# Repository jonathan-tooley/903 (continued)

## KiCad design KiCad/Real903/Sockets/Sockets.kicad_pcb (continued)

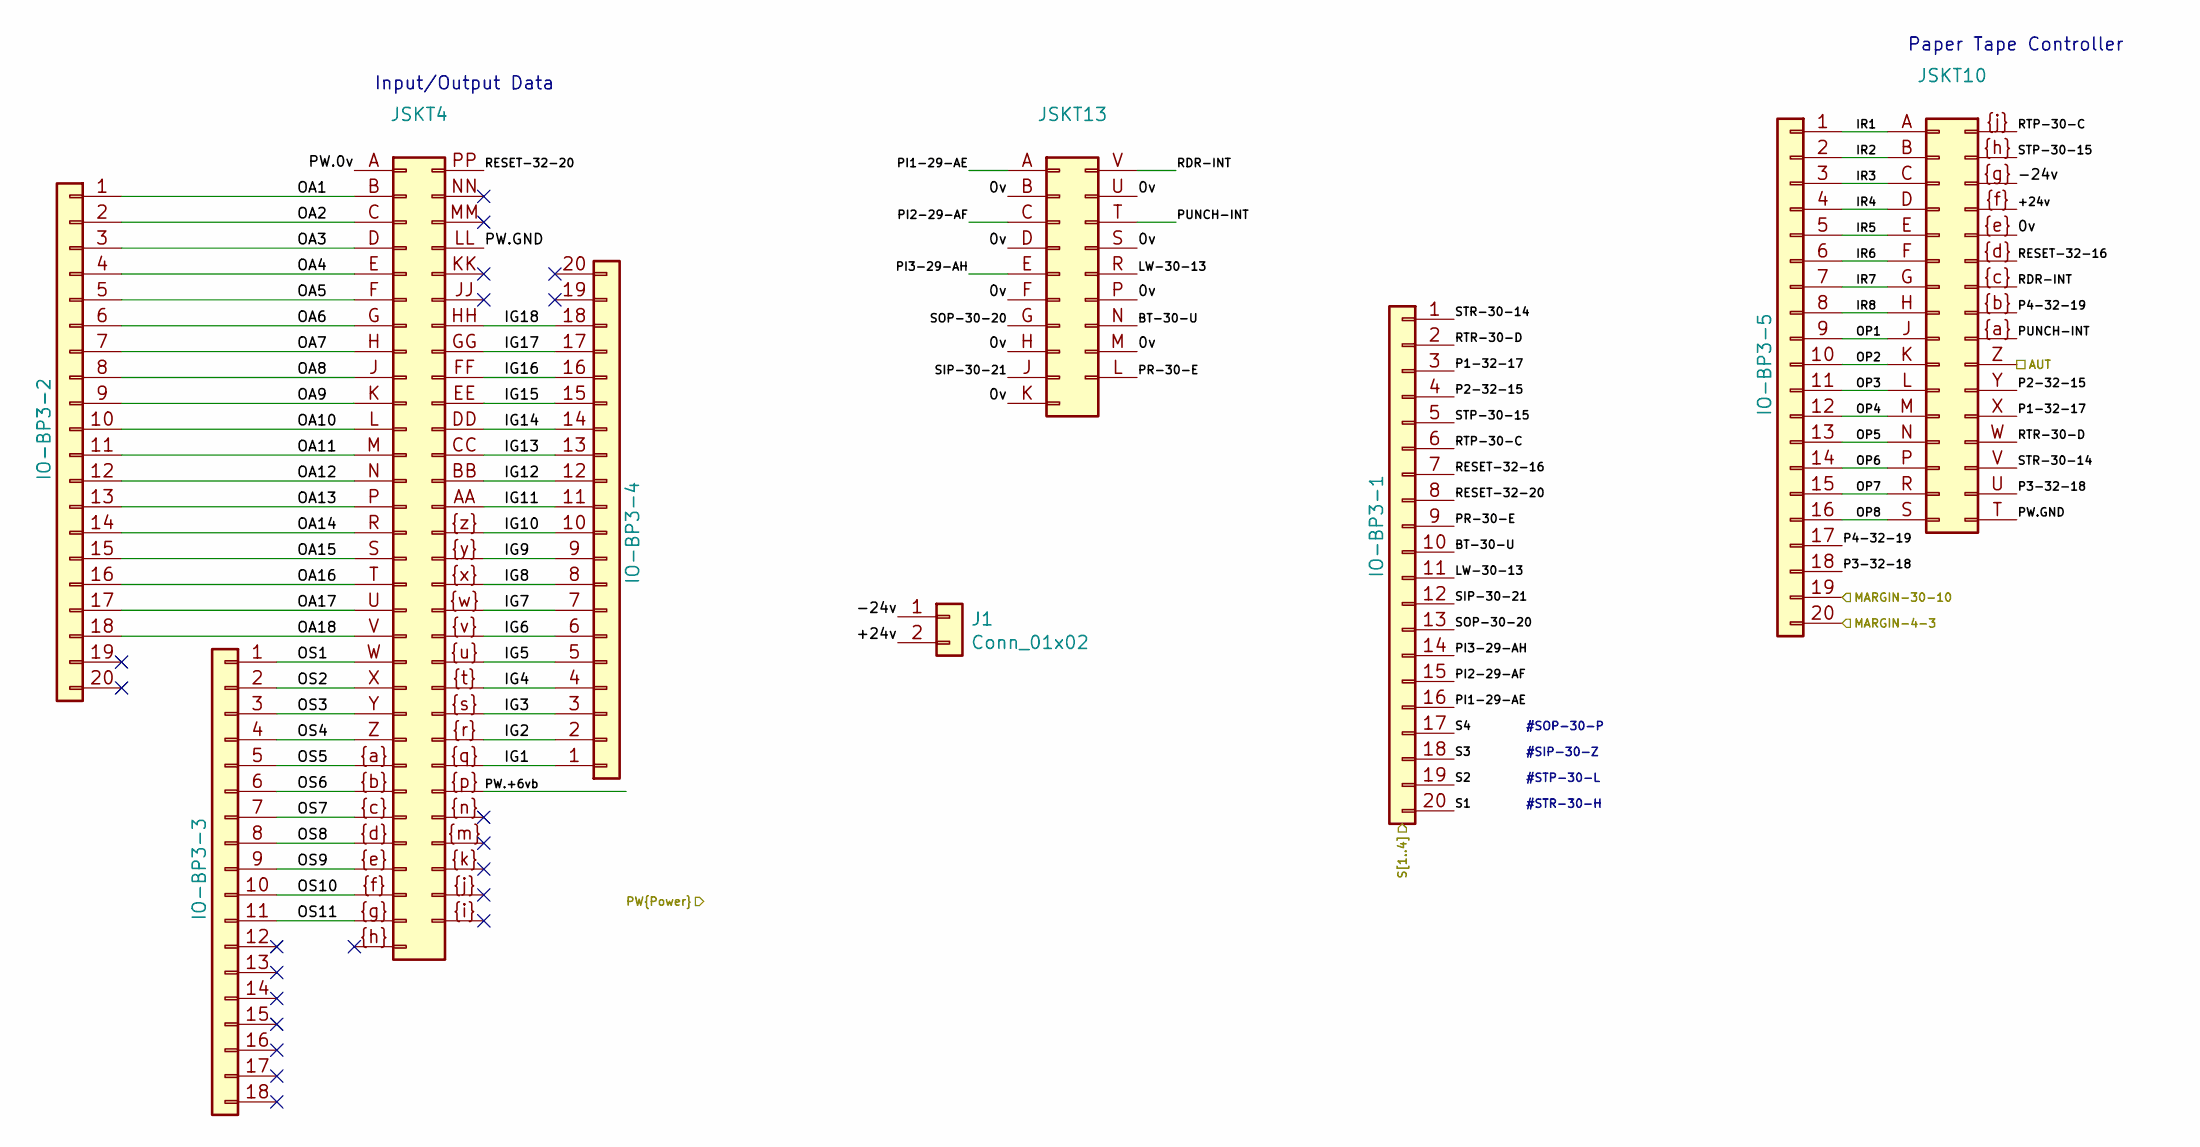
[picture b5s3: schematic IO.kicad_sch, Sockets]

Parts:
IO-BP3-1, IO-BP3-2, IO-BP3-3, IO-BP3-4, IO-BP3-5: IDC-Header_2x10_P2.54mm_Vertical
J1: Conn_01x02
JSKT4: MC61
JSKT10: MC32
JSKT13: (no value)

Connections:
/Control Unit/AUT: JSKT10.Z; also elsewhere on the board
/Control Unit/MARGIN-4-3: IO-BP3-5.20; also elsewhere on the board
/Control Unit/PW.0v: JSKT4.A; also elsewhere on the board
/Control Unit/PW.+6vb: JSKT4.~{p}; also elsewhere on the board
/Control Unit/PW.GND: JSKT4.LL, JSKT10.T; also elsewhere on the board
/Display/S1: IO-BP3-1.20; also elsewhere on the board
/Display/S2: IO-BP3-1.19; also elsewhere on the board
/Display/S3: IO-BP3-1.18; also elsewhere on the board
/Display/S4: IO-BP3-1.17; also elsewhere on the board
/IO/0v: JSKT10.~{e}, JSKT13.B, JSKT13.D, JSKT13.F, JSKT13.H, JSKT13.K, JSKT13.M, JSKT13.P, JSKT13.S, JSKT13.U
/IO/+24v: J1.2, JSKT10.~{f}
/IO/-24v: J1.1, JSKT10.~{g}
/IO/BT-30-U: IO-BP3-1.10, JSKT13.N
/IO/IG1: IO-BP3-4.1, JSKT4.~{q}
/IO/IG2: IO-BP3-4.2, JSKT4.~{r}
/IO/IG3: IO-BP3-4.3, JSKT4.~{s}
/IO/IG4: IO-BP3-4.4, JSKT4.~{t}
/IO/IG5: IO-BP3-4.5, JSKT4.~{u}
/IO/IG6: IO-BP3-4.6, JSKT4.~{v}
/IO/IG7: IO-BP3-4.7, JSKT4.~{w}
/IO/IG8: IO-BP3-4.8, JSKT4.~{x}
/IO/IG9: IO-BP3-4.9, JSKT4.~{y}
/IO/IG10: IO-BP3-4.10, JSKT4.~{z}
/IO/IG11: IO-BP3-4.11, JSKT4.AA
/IO/IG12: IO-BP3-4.12, JSKT4.BB
/IO/IG13: IO-BP3-4.13, JSKT4.CC
/IO/IG14: IO-BP3-4.14, JSKT4.DD
/IO/IG15: IO-BP3-4.15, JSKT4.EE
/IO/IG16: IO-BP3-4.16, JSKT4.FF
/IO/IG17: IO-BP3-4.17, JSKT4.GG
/IO/IG18: IO-BP3-4.18, JSKT4.HH
/IO/IR1: IO-BP3-5.1, JSKT10.A
/IO/IR2: IO-BP3-5.2, JSKT10.B
/IO/IR3: IO-BP3-5.3, JSKT10.C
/IO/IR4: IO-BP3-5.4, JSKT10.D
/IO/IR5: IO-BP3-5.5, JSKT10.E
/IO/IR6: IO-BP3-5.6, JSKT10.F
/IO/IR7: IO-BP3-5.7, JSKT10.G
/IO/IR8: IO-BP3-5.8, JSKT10.H
/IO/LW-30-13: IO-BP3-1.11, JSKT13.R
/IO/MARGIN-30-10: IO-BP3-5.19; also elsewhere on the board
/IO/OA1: IO-BP3-2.1, JSKT4.B
/IO/OA2: IO-BP3-2.2, JSKT4.C
/IO/OA3: IO-BP3-2.3, JSKT4.D
/IO/OA4: IO-BP3-2.4, JSKT4.E
/IO/OA5: IO-BP3-2.5, JSKT4.F
/IO/OA6: IO-BP3-2.6, JSKT4.G
/IO/OA7: IO-BP3-2.7, JSKT4.H
/IO/OA8: IO-BP3-2.8, JSKT4.J
/IO/OA9: IO-BP3-2.9, JSKT4.K
/IO/OA10: IO-BP3-2.10, JSKT4.L
/IO/OA11: IO-BP3-2.11, JSKT4.M
/IO/OA12: IO-BP3-2.12, JSKT4.N
/IO/OA13: IO-BP3-2.13, JSKT4.P
/IO/OA14: IO-BP3-2.14, JSKT4.R
/IO/OA15: IO-BP3-2.15, JSKT4.S
/IO/OA16: IO-BP3-2.16, JSKT4.T
/IO/OA17: IO-BP3-2.17, JSKT4.U
/IO/OA18: IO-BP3-2.18, JSKT4.V
/IO/OP1: IO-BP3-5.9, JSKT10.J
/IO/OP2: IO-BP3-5.10, JSKT10.K
/IO/OP3: IO-BP3-5.11, JSKT10.L
/IO/OP4: IO-BP3-5.12, JSKT10.M
/IO/OP5: IO-BP3-5.13, JSKT10.N
/IO/OP6: IO-BP3-5.14, JSKT10.P
/IO/OP7: IO-BP3-5.15, JSKT10.R
/IO/OP8: IO-BP3-5.16, JSKT10.S
/IO/OS1: IO-BP3-3.1, JSKT4.W
/IO/OS2: IO-BP3-3.2, JSKT4.X
/IO/OS3: IO-BP3-3.3, JSKT4.Y
/IO/OS4: IO-BP3-3.4, JSKT4.Z
/IO/OS5: IO-BP3-3.5, JSKT4.~{a}
/IO/OS6: IO-BP3-3.6, JSKT4.~{b}
/IO/OS7~{: IO-BP3-3.7, JSKT4.~{c}
/IO/OS8: IO-BP3-3.8, JSKT4.~{d}
/IO/OS9: IO-BP3-3.9, JSKT4.~{e}
/IO/OS10: IO-BP3-3.10, JSKT4.~{f}
/IO/OS11: IO-BP3-3.11, JSKT4.~{g}
/IO/P1-32-17: IO-BP3-1.3, JSKT10.X
/IO/P2-32-15: IO-BP3-1.4, JSKT10.Y
/IO/P3-32-18: IO-BP3-5.18, JSKT10.U
/IO/P4-32-19: IO-BP3-5.17, JSKT10.~{b}
/IO/PI1-29-AE: IO-BP3-1.16, JSKT13.A
/IO/PI2-29-AF: IO-BP3-1.15, JSKT13.C
/IO/PI3-29-AH: IO-BP3-1.14, JSKT13.E
/IO/PR-30-E: IO-BP3-1.9, JSKT13.L
/IO/PUNCH-INT: JSKT10.~{a}, JSKT13.T
/IO/RDR-INT: JSKT10.~{c}, JSKT13.V
/IO/RESET-32-16: IO-BP3-1.7, JSKT10.~{d}
/IO/RESET-32-20: IO-BP3-1.8, JSKT4.PP
/IO/RTP-30-C: IO-BP3-1.6, JSKT10.~{j}
/IO/RTR-30-D: IO-BP3-1.2, JSKT10.W
/IO/SIP-30-21: IO-BP3-1.12, JSKT13.J
/IO/SOP-30-20: IO-BP3-1.13, JSKT13.G
/IO/STP-30-15: IO-BP3-1.5, JSKT10.~{h}
/IO/STR-30-14: IO-BP3-1.1, JSKT10.V

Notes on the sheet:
#SIP-30-Z
#STR-30-H
#STP-30-L
Input/Output Data
#SOP-30-P
Paper Tape Controller

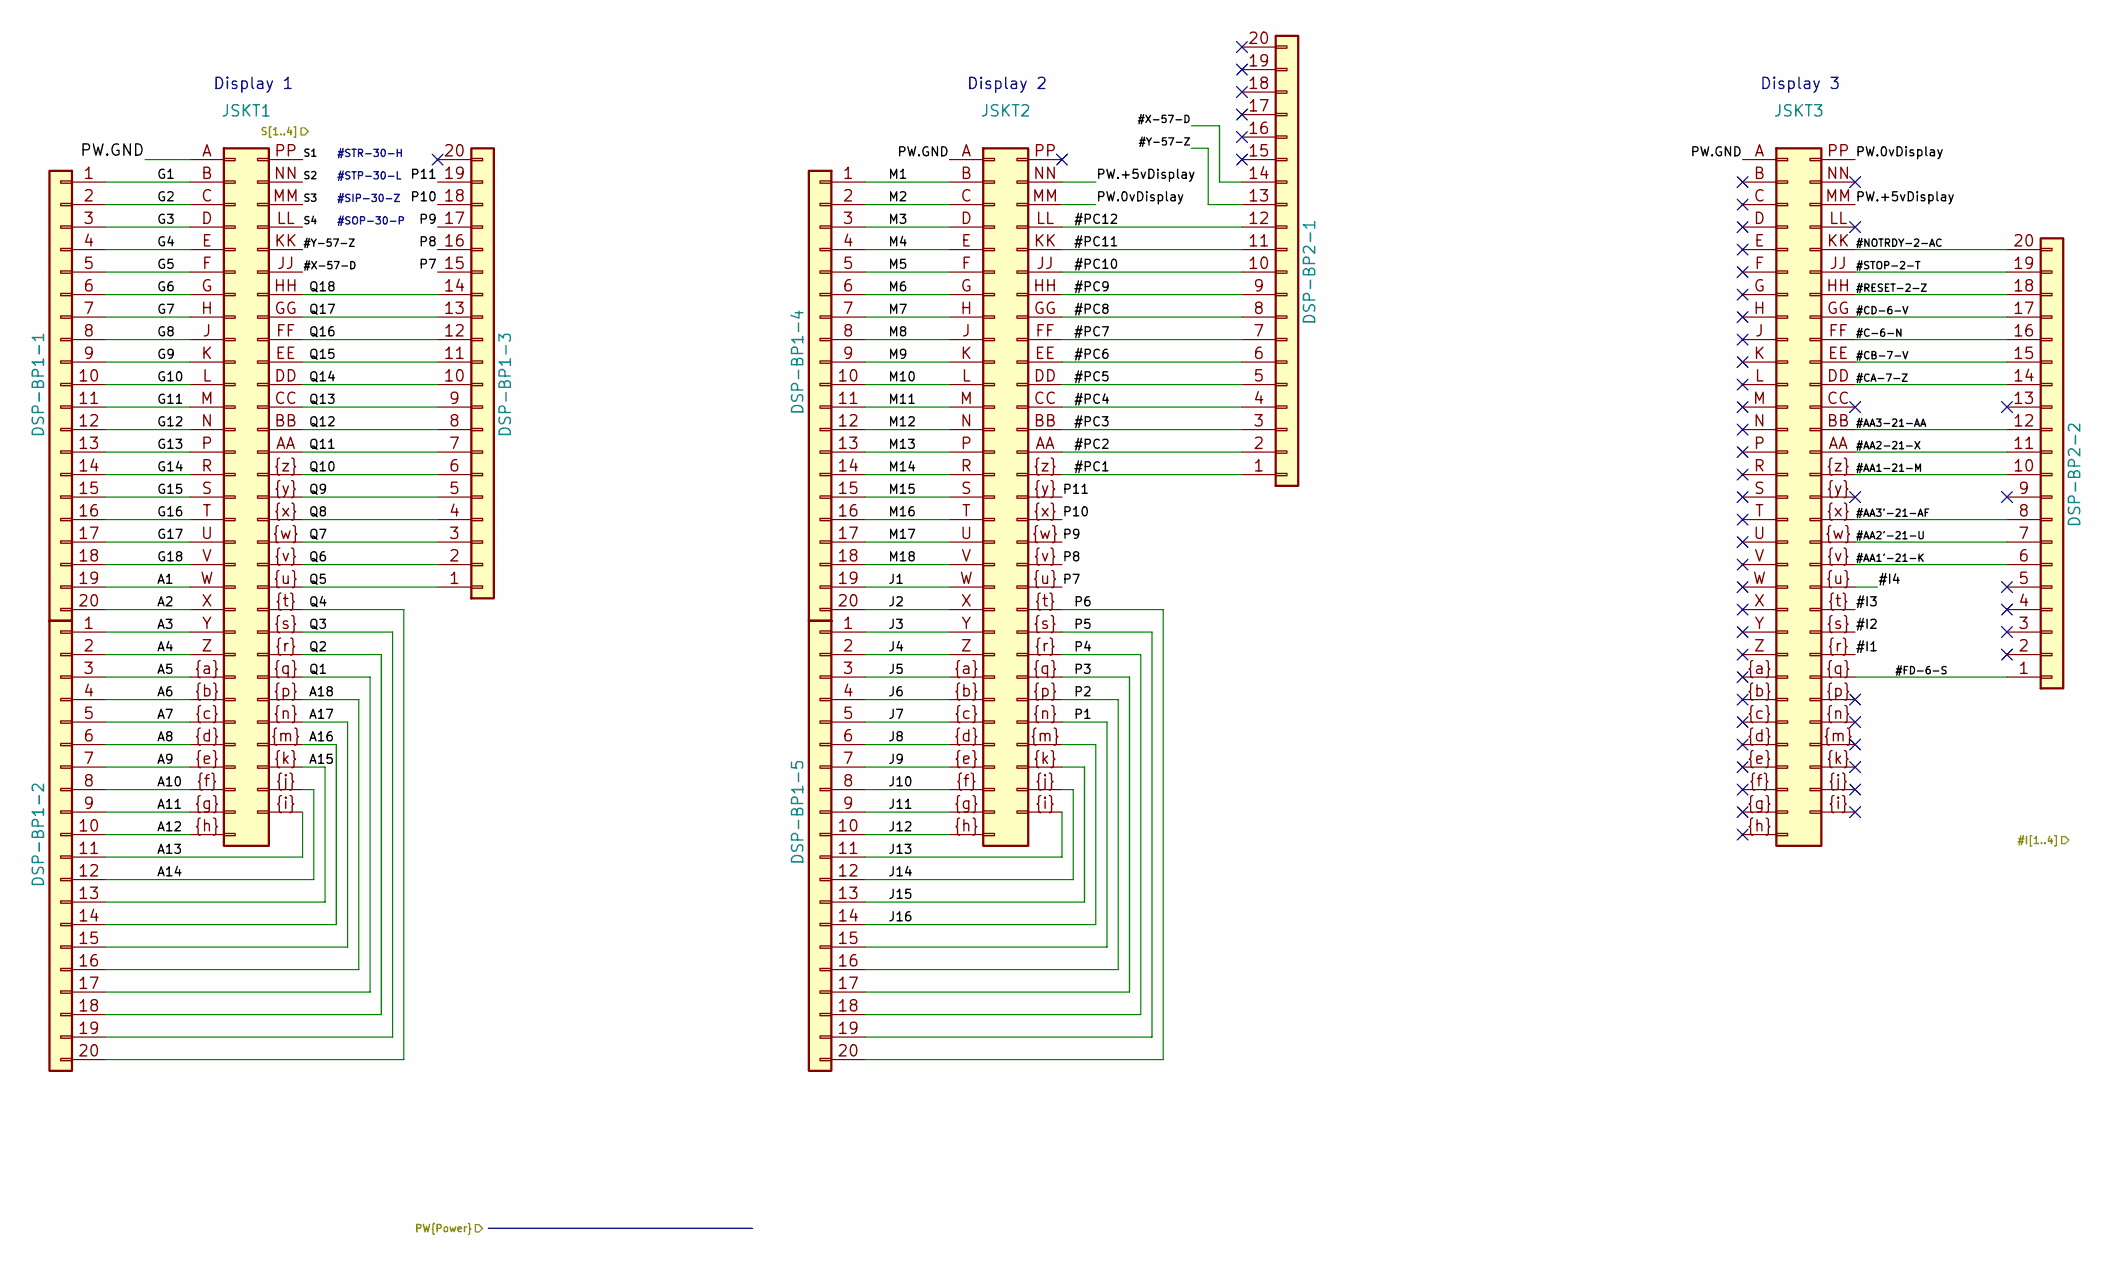
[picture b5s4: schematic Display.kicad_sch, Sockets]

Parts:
DSP-BP1-1, DSP-BP1-2, DSP-BP1-3, DSP-BP1-4, DSP-BP1-5, DSP-BP2-1, DSP-BP2-2: IDC-Header_2x10_P2.54mm_Vertical
JSKT1, JSKT2, JSKT3: MC61

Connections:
/Control Unit/#I1: JSKT3.~{r}; also elsewhere on the board
/Control Unit/#I2: JSKT3.~{s}; also elsewhere on the board
/Control Unit/#I3: JSKT3.~{t}; also elsewhere on the board
/Control Unit/#I4: JSKT3.~{u}; also elsewhere on the board
/Control Unit/PW.0vDisplay: JSKT2.MM, JSKT3.PP; also elsewhere on the board
/Control Unit/PW.+5vDisplay: JSKT2.NN, JSKT3.MM; also elsewhere on the board
/Control Unit/PW.GND: JSKT1.A, JSKT2.A, JSKT3.A; also elsewhere on the board
/Display/#AA1'-21-K: DSP-BP2-2.6, JSKT3.~{v}
/Display/#AA1-21-M: DSP-BP2-2.10, JSKT3.~{z}
/Display/#AA2'-21-U: DSP-BP2-2.7, JSKT3.~{w}
/Display/#AA2-21-X: DSP-BP2-2.11, JSKT3.AA
/Display/#AA3'-21-AF: DSP-BP2-2.8, JSKT3.~{x}
/Display/#AA3-21-AA: DSP-BP2-2.12, JSKT3.BB
/Display/#C-6-N: DSP-BP2-2.16, JSKT3.FF
/Display/#CA-7-Z: DSP-BP2-2.14, JSKT3.DD
/Display/#CB-7-V: DSP-BP2-2.15, JSKT3.EE
/Display/#CD-6-V: DSP-BP2-2.17, JSKT3.GG
/Display/#FD-6-S: DSP-BP2-2.1, JSKT3.~{q}
/Display/#NOTRDY-2-AC: DSP-BP2-2.20, JSKT3.KK
/Display/#PC1: DSP-BP2-1.1, JSKT2.~{z}
/Display/#PC2: DSP-BP2-1.2, JSKT2.AA
/Display/#PC3: DSP-BP2-1.3, JSKT2.BB
/Display/#PC4: DSP-BP2-1.4, JSKT2.CC
/Display/#PC5: DSP-BP2-1.5, JSKT2.DD
/Display/#PC6: DSP-BP2-1.6, JSKT2.EE
/Display/#PC7: DSP-BP2-1.7, JSKT2.FF
/Display/#PC8: DSP-BP2-1.8, JSKT2.GG
/Display/#PC9: DSP-BP2-1.9, JSKT2.HH
/Display/#PC10: DSP-BP2-1.10, JSKT2.JJ
/Display/#PC11: DSP-BP2-1.11, JSKT2.KK
/Display/#PC12: DSP-BP2-1.12, JSKT2.LL
/Display/#RESET-2-Z: DSP-BP2-2.18, JSKT3.HH
/Display/#STOP-2-T: DSP-BP2-2.19, JSKT3.JJ
/Display/#X-57-D: DSP-BP2-1.14, JSKT1.JJ
/Display/#Y-57-Z: DSP-BP2-1.13, JSKT1.KK
/Display/A1: DSP-BP1-1.19, JSKT1.W
/Display/A2: DSP-BP1-1.20, JSKT1.X
/Display/A3: DSP-BP1-2.1, JSKT1.Y
/Display/A4: DSP-BP1-2.2, JSKT1.Z
/Display/A5: DSP-BP1-2.3, JSKT1.~{a}
/Display/A6: DSP-BP1-2.4, JSKT1.~{b}
/Display/A7: DSP-BP1-2.5, JSKT1.~{c}
/Display/A8: DSP-BP1-2.6, JSKT1.~{d}
/Display/A9: DSP-BP1-2.7, JSKT1.~{e}
/Display/A10: DSP-BP1-2.8, JSKT1.~{f}
/Display/A11: DSP-BP1-2.9, JSKT1.~{g}
/Display/A12: DSP-BP1-2.10, JSKT1.~{h}
/Display/A13: DSP-BP1-2.11, JSKT1.~{i}
/Display/A14: DSP-BP1-2.12, JSKT1.~{j}
/Display/A15: DSP-BP1-2.13, JSKT1.~{k}
/Display/A16: DSP-BP1-2.14, JSKT1.~{m}
/Display/A17: DSP-BP1-2.15, JSKT1.~{n}
/Display/A18: DSP-BP1-2.16, JSKT1.~{p}
/Display/G1: DSP-BP1-1.1, JSKT1.B
/Display/G2: DSP-BP1-1.2, JSKT1.C
/Display/G3: DSP-BP1-1.3, JSKT1.D
/Display/G4: DSP-BP1-1.4, JSKT1.E
/Display/G5: DSP-BP1-1.5, JSKT1.F
/Display/G6: DSP-BP1-1.6, JSKT1.G
/Display/G7: DSP-BP1-1.7, JSKT1.H
/Display/G8: DSP-BP1-1.8, JSKT1.J
/Display/G9: DSP-BP1-1.9, JSKT1.K
/Display/G10: DSP-BP1-1.10, JSKT1.L
/Display/G11: DSP-BP1-1.11, JSKT1.M
/Display/G12: DSP-BP1-1.12, JSKT1.N
/Display/G13: DSP-BP1-1.13, JSKT1.P
/Display/G14: DSP-BP1-1.14, JSKT1.R
/Display/G15: DSP-BP1-1.15, JSKT1.S
/Display/G16: DSP-BP1-1.16, JSKT1.T
/Display/G17: DSP-BP1-1.17, JSKT1.U
/Display/G18: DSP-BP1-1.18, JSKT1.V
/Display/J1: DSP-BP1-4.19, JSKT2.W
/Display/J2: DSP-BP1-4.20, JSKT2.X
/Display/J3: DSP-BP1-5.1, JSKT2.Y
/Display/J4: DSP-BP1-5.2, JSKT2.Z
/Display/J5: DSP-BP1-5.3, JSKT2.~{a}
/Display/J6: DSP-BP1-5.4, JSKT2.~{b}
/Display/J7: DSP-BP1-5.5, JSKT2.~{c}
/Display/J8: DSP-BP1-5.6, JSKT2.~{d}
/Display/J9: DSP-BP1-5.7, JSKT2.~{e}
/Display/J10: DSP-BP1-5.8, JSKT2.~{f}
/Display/J11: DSP-BP1-5.9, JSKT2.~{g}
/Display/J12: DSP-BP1-5.10, JSKT2.~{h}
/Display/J13: DSP-BP1-5.11, JSKT2.~{i}
/Display/J14: DSP-BP1-5.12, JSKT2.~{j}
/Display/J15: DSP-BP1-5.13, JSKT2.~{k}
/Display/J16: DSP-BP1-5.14, JSKT2.~{m}
/Display/M1: DSP-BP1-4.1, JSKT2.B
/Display/M2: DSP-BP1-4.2, JSKT2.C
/Display/M3: DSP-BP1-4.3, JSKT2.D
/Display/M4: DSP-BP1-4.4, JSKT2.E
/Display/M5: DSP-BP1-4.5, JSKT2.F
/Display/M6: DSP-BP1-4.6, JSKT2.G
/Display/M7: DSP-BP1-4.7, JSKT2.H
/Display/M8: DSP-BP1-4.8, JSKT2.J
/Display/M9: DSP-BP1-4.9, JSKT2.K
/Display/M10: DSP-BP1-4.10, JSKT2.L
/Display/M11: DSP-BP1-4.11, JSKT2.M
/Display/M12: DSP-BP1-4.12, JSKT2.N
/Display/M13: DSP-BP1-4.13, JSKT2.P
/Display/M14: DSP-BP1-4.14, JSKT2.R
/Display/M15: DSP-BP1-4.15, JSKT2.S
/Display/M16: DSP-BP1-4.16, JSKT2.T
/Display/M17: DSP-BP1-4.17, JSKT2.U
/Display/M18: DSP-BP1-4.18, JSKT2.V
/Display/P1: DSP-BP1-5.15, JSKT2.~{n}
/Display/P2: DSP-BP1-5.16, JSKT2.~{p}
/Display/P3: DSP-BP1-5.17, JSKT2.~{q}
/Display/P4: DSP-BP1-5.18, JSKT2.~{r}
/Display/P5: DSP-BP1-5.19, JSKT2.~{s}
/Display/P6: DSP-BP1-5.20, JSKT2.~{t}
/Display/P7: DSP-BP1-3.15, JSKT2.~{u}
/Display/P8: DSP-BP1-3.16, JSKT2.~{v}
/Display/P9: DSP-BP1-3.17, JSKT2.~{w}
/Display/P10: DSP-BP1-3.18, JSKT2.~{x}
/Display/P11: DSP-BP1-3.19, JSKT2.~{y}
/Display/Q1: DSP-BP1-2.17, JSKT1.~{q}
/Display/Q2: DSP-BP1-2.18, JSKT1.~{r}
/Display/Q3: DSP-BP1-2.19, JSKT1.~{s}
/Display/Q4: DSP-BP1-2.20, JSKT1.~{t}
/Display/Q5: DSP-BP1-3.1, JSKT1.~{u}
/Display/Q6: DSP-BP1-3.2, JSKT1.~{v}
/Display/Q7: DSP-BP1-3.3, JSKT1.~{w}
/Display/Q8: DSP-BP1-3.4, JSKT1.~{x}
/Display/Q9: DSP-BP1-3.5, JSKT1.~{y}
/Display/Q10: DSP-BP1-3.6, JSKT1.~{z}
/Display/Q11: DSP-BP1-3.7, JSKT1.AA
/Display/Q12: DSP-BP1-3.8, JSKT1.BB
/Display/Q13: DSP-BP1-3.9, JSKT1.CC
/Display/Q14: DSP-BP1-3.10, JSKT1.DD
/Display/Q15: DSP-BP1-3.11, JSKT1.EE
/Display/Q16: DSP-BP1-3.12, JSKT1.FF
/Display/Q17: DSP-BP1-3.13, JSKT1.GG
/Display/Q18: DSP-BP1-3.14, JSKT1.HH
/Display/S1: JSKT1.PP; also elsewhere on the board
/Display/S2: JSKT1.NN; also elsewhere on the board
/Display/S3: JSKT1.MM; also elsewhere on the board
/Display/S4: JSKT1.LL; also elsewhere on the board

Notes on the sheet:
Display 1
#SIP-30-Z
#STR-30-H
Display 2
#STP-30-L
Display 3
#SOP-30-P

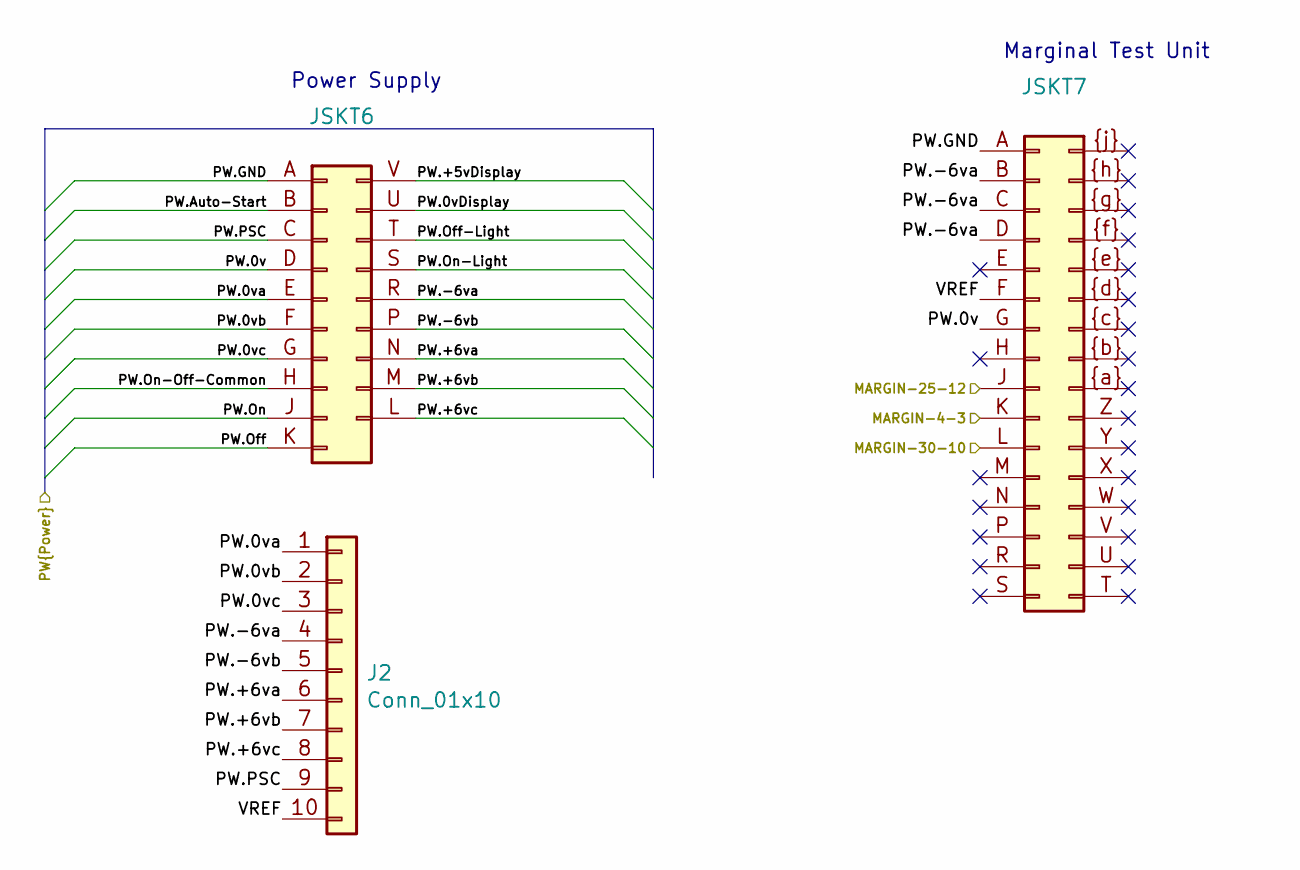
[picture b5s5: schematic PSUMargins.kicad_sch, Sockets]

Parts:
J2: Conn_01x10; Wago_734-140_1x10_P3.50mm_Vertical
JSKT6: MC19
JSKT7: MC32

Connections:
/Control Unit/MARGIN-4-3: JSKT7.K; also elsewhere on the board
/Control Unit/PW.0v: JSKT6.D, JSKT7.G; also elsewhere on the board
/Control Unit/PW.0vDisplay: JSKT6.U; also elsewhere on the board
/Control Unit/PW.0va: J2.1, JSKT6.E
/Control Unit/PW.0vb: J2.2, JSKT6.F
/Control Unit/PW.0vc: J2.3, JSKT6.G
/Control Unit/PW.+5vDisplay: JSKT6.V; also elsewhere on the board
/Control Unit/PW.+6va: J2.6, JSKT6.N; also elsewhere on the board
/Control Unit/PW.+6vb: J2.7, JSKT6.M; also elsewhere on the board
/Control Unit/PW.+6vc: J2.8, JSKT6.L
/Control Unit/PW.-6va: J2.4, JSKT6.R, JSKT7.B, JSKT7.C, JSKT7.D; also elsewhere on the board
/Control Unit/PW.-6vb: J2.5, JSKT6.P
/Control Unit/PW.Auto-Start: JSKT6.B; also elsewhere on the board
/Control Unit/PW.GND: JSKT6.A, JSKT7.A; also elsewhere on the board
/Control Unit/PW.Off: JSKT6.K; also elsewhere on the board
/Control Unit/PW.Off-Light: JSKT6.T; also elsewhere on the board
/Control Unit/PW.On: JSKT6.J; also elsewhere on the board
/Control Unit/PW.On-Light: JSKT6.S; also elsewhere on the board
/Control Unit/PW.On-Off-Common: JSKT6.H; also elsewhere on the board
/Control Unit/PW.PSC: J2.9, JSKT6.C
/IO/MARGIN-30-10: JSKT7.L; also elsewhere on the board
/PSUMargins/MARGIN-25-12: JSKT7.J
/PSUMargins/VREF: J2.10, JSKT7.F

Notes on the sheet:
Power Supply
Marginal Test Unit

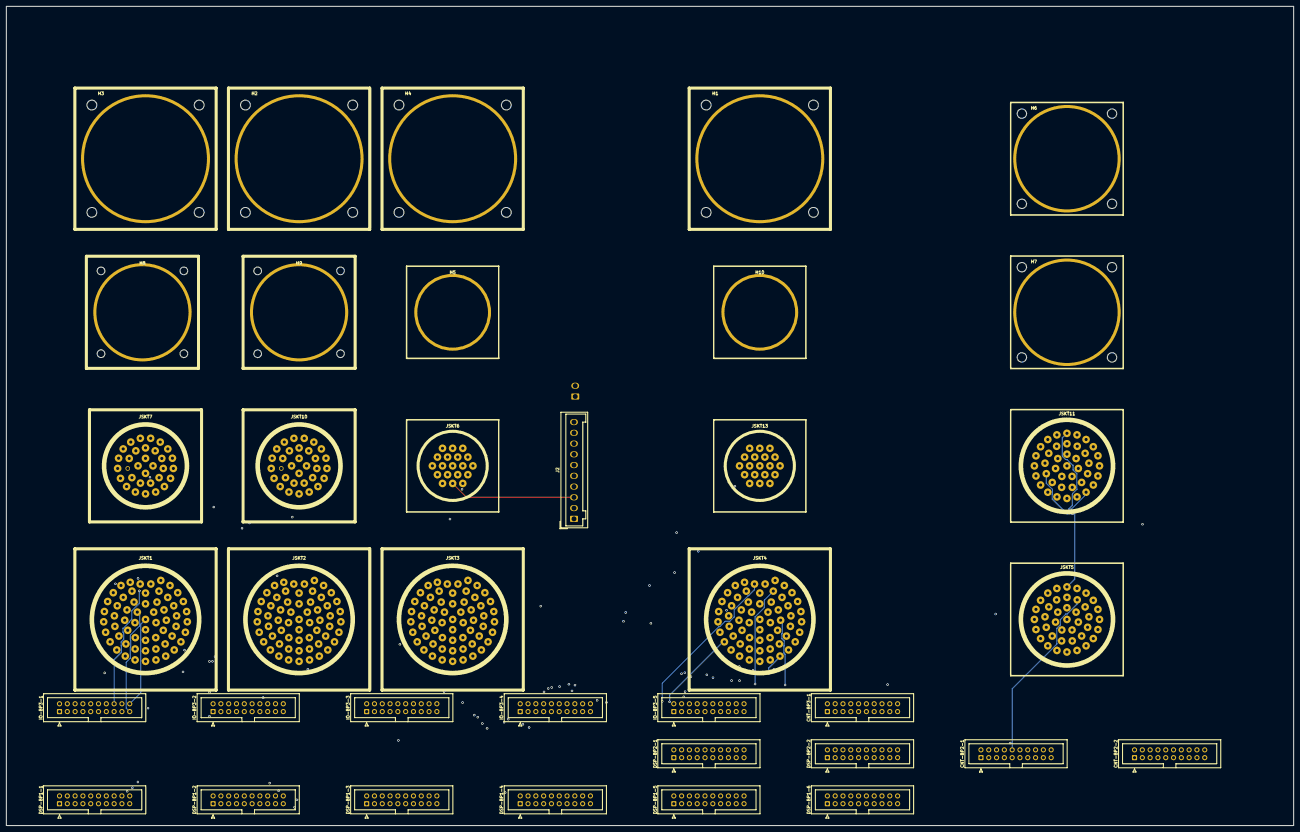
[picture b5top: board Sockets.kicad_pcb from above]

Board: 4 copper layers, 419.1 x 266.7 mm, 38 parts (1 on the bottom side), 296 nets.

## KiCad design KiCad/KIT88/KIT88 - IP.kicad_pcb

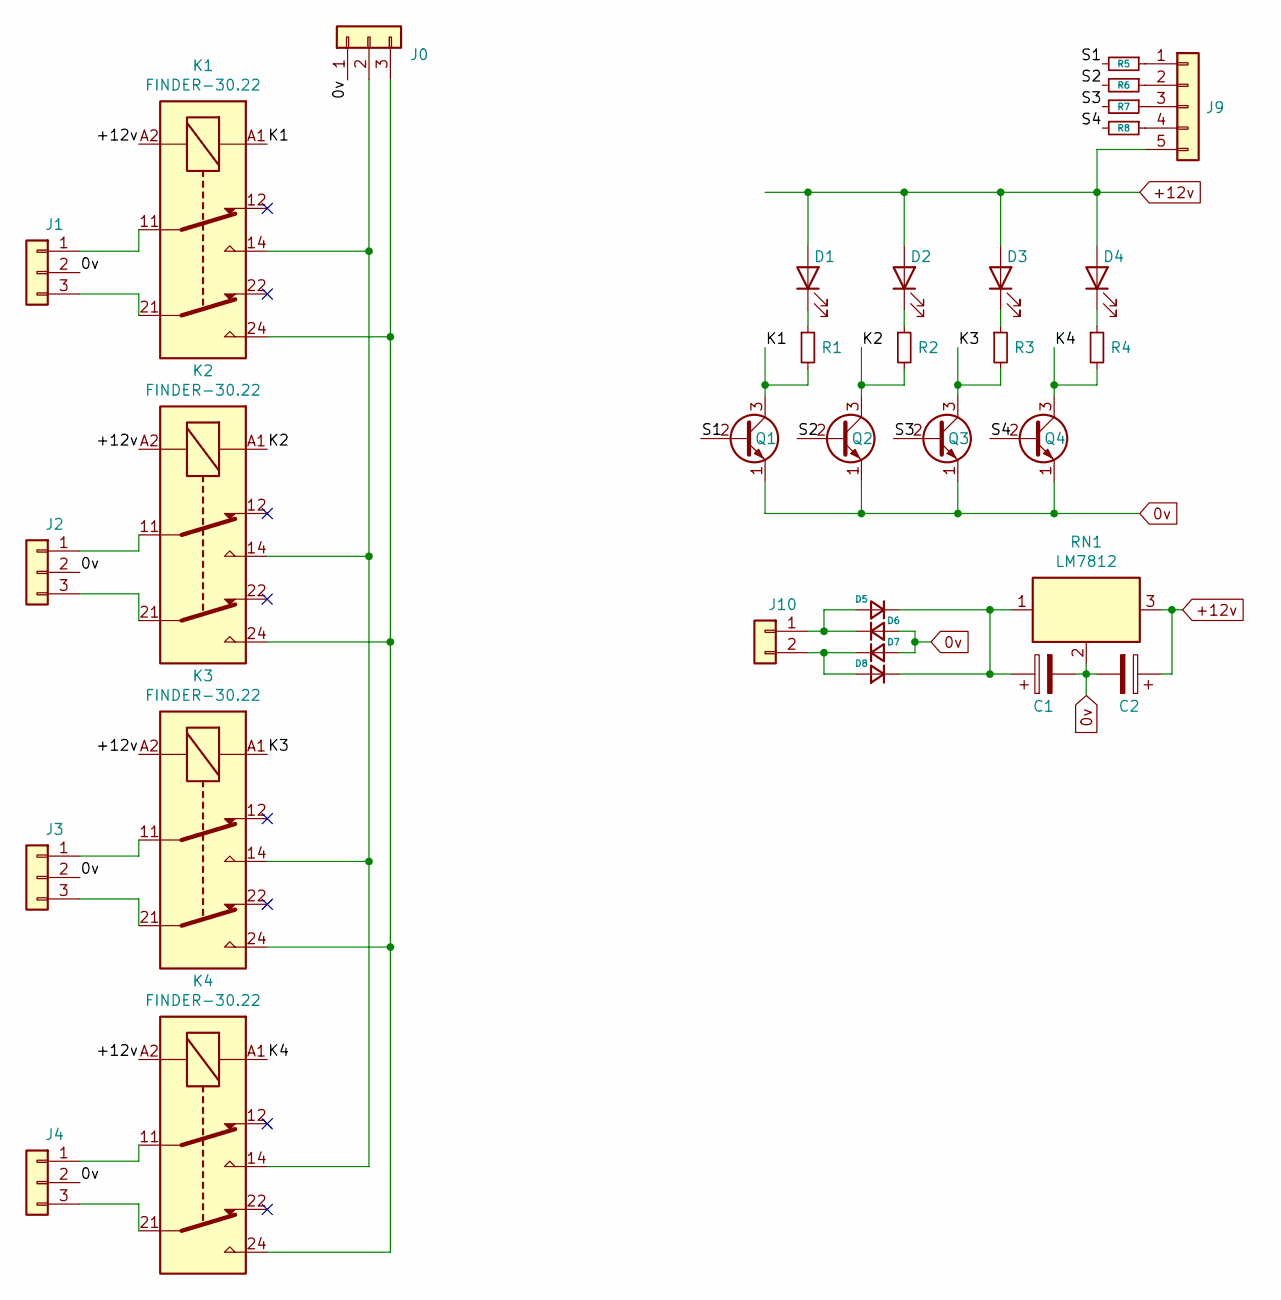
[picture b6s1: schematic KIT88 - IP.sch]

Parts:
C1, C2: CP_Radial_D6.3mm_P2.50mm
D1, D2, D3, D4: LED_D4.0mm
D5, D6, D7, D8: D_DO-34_SOD68_P7.62mm_Horizontal
J0: PinSocket_1x03_P2.54mm_Vertical
J1, J2, J3, J4: RCA
J9: PinSocket_1x05_P2.54mm_Vertical
J10: PinSocket_1x02_P2.54mm_Vertical
K1, K2, K3, K4: FINDER-30.22; Relay_DPDT_Finder_30.22
Q1, Q2, Q3, Q4: TO-92
R1, R2, R3, R4, R5, R6, R7, R8: R_Axial_DIN0204_L3.6mm_D1.6mm_P7.62mm_Horizontal
RN1: LM7812; TO-220-3_Vertical

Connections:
0v: C1.2, C2.2, D6.2 (A), D7.2 (A), J0.1, J1.2, J2.2, J3.2, J4.2, Q1.1 (E), Q2.1 (E), Q3.1 (E), Q4.1 (E), RN1.2
+12v: C2.1, D1.2 (A), D2.2 (A), D3.2 (A), D4.2 (A), J9.5, K1.A2, K2.A2, K3.A2, K4.A2, RN1.3
/K1: K1.A1, Q1.3 (C), R1.2
/K2: K2.A1, Q2.3 (C), R2.2
/K3: K3.A1, Q3.3 (C), R3.2
/K4: K4.A1, Q4.3 (C), R4.2
/S1: Q1.2 (B), R5.2
/S2: Q2.2 (B), R6.2
/S3: Q3.2 (B), R7.2
/S4: Q4.2 (B), R8.2
unnamed: C1.1, D5.1 (K), D8.1 (K), RN1.1
unnamed: D1.1 (K), R1.1
unnamed: D2.1 (K), R2.1
unnamed: D3.1 (K), R3.1
unnamed: D4.1 (K), R4.1
unnamed: D5.2 (A), D6.1 (K), J10.1
unnamed: D7.1 (K), D8.2 (A), J10.2
unnamed: J0.2, K1.14, K2.14, K3.14, K4.14
unnamed: J0.3, K1.24, K2.24, K3.24, K4.24
unnamed: J1.1, K1.11
unnamed: J1.3, K1.21
unnamed: J2.1, K2.11
unnamed: J2.3, K2.21
unnamed: J3.1, K3.11
unnamed: J3.3, K3.21
unnamed: J4.1, K4.11
unnamed: J4.3, K4.21
unnamed: J9.1, R5.1
unnamed: J9.2, R6.1
unnamed: J9.3, R7.1
unnamed: J9.4, R8.1

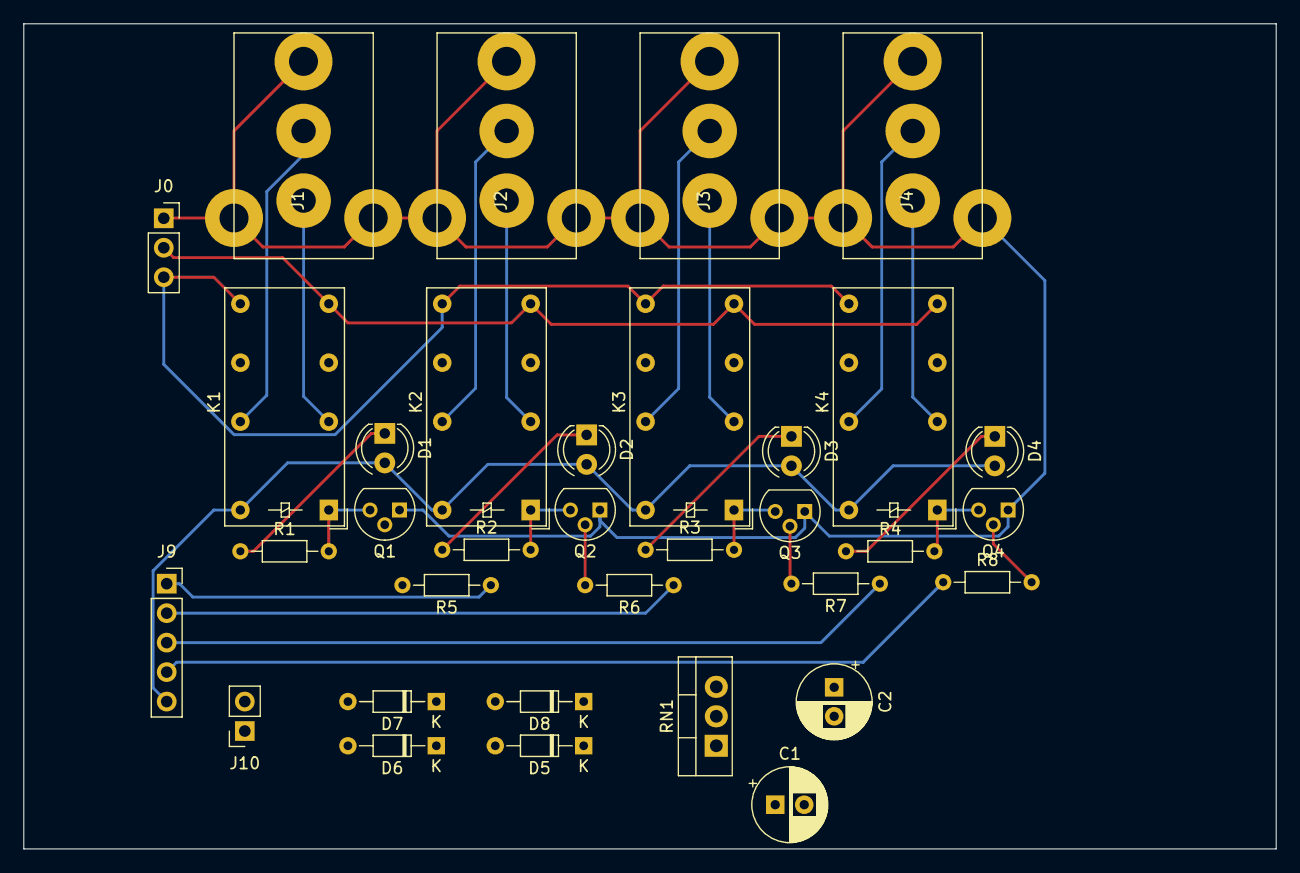
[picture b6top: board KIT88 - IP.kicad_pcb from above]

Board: 2 copper layers, 108.0 x 71.1 mm, 34 parts (0 on the bottom side), 31 nets.

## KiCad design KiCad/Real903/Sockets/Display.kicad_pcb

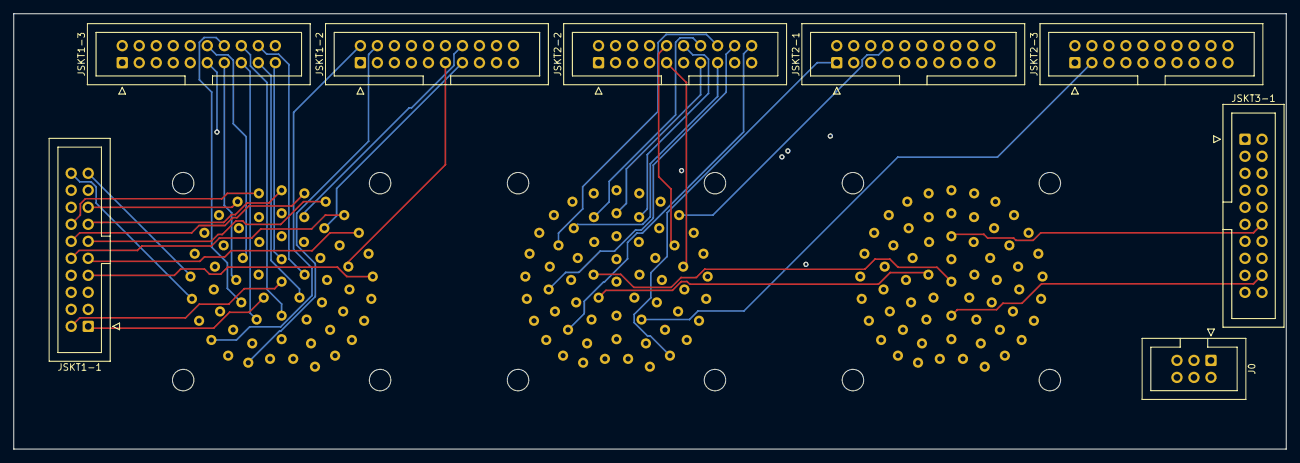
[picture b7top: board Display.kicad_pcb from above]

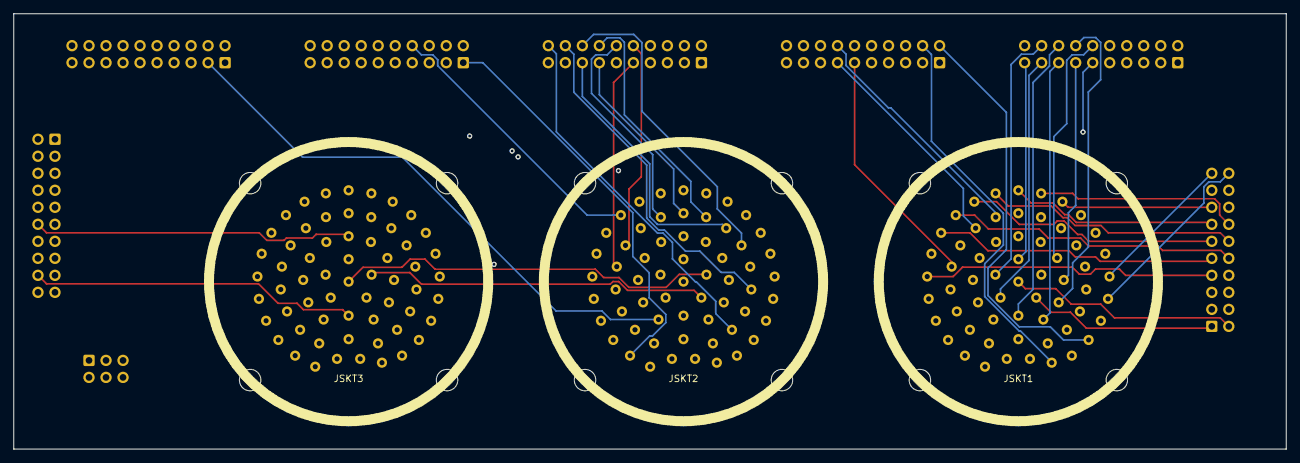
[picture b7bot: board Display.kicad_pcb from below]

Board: 4 copper layers, 190.0 x 65.0 mm, 11 parts (3 on the bottom side), 138 nets.

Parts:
J0: IDC-Header_2x03_P2.54mm_Vertical
JSKT1: MC61
JSKT1-1, JSKT1-2, JSKT1-3, JSKT2-1, JSKT2-2, JSKT2-3, JSKT3-1: IDC-Header_2x10_P2.54mm_Vertical
JSKT2, JSKT3: Circ61; MC61

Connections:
/Display/0vDisplay: J0.1, JSKT2.MM, JSKT3.PP
/Display/#AA1'-21-K: JSKT3.~v~, JSKT3-1.6
/Display/#AA1-21-M: JSKT3.~z~, JSKT3-1.10
/Display/#AA2'-21-U: JSKT3.~w~, JSKT3-1.7
/Display/#AA2-21-X: JSKT3.AA, JSKT3-1.11
/Display/#AA3'-21-AF: JSKT3.~x~, JSKT3-1.8
/Display/#AA3-21-AA: JSKT3.BB, JSKT3-1.12
/Display/#C-6-N: JSKT3.FF, JSKT3-1.16
/Display/#CA-7-Z: JSKT3.DD, JSKT3-1.14
/Display/#CB-7-V: JSKT3.EE, JSKT3-1.15
/Display/#CD-6-V: JSKT3.GG, JSKT3-1.17
/Display/#FD-6-S: JSKT3.~q~, JSKT3-1.1
/Display/#I1: JSKT3.~r~, JSKT3-1.2
/Display/#I2: JSKT3.~s~, JSKT3-1.3
/Display/#I3: JSKT3.~t~, JSKT3-1.4
/Display/#I4: JSKT3.~u~, JSKT3-1.5
/Display/#NOTRDY-2-AC: JSKT3.KK, JSKT3-1.20
/Display/#PC1: JSKT2.~z~, JSKT2-3.6
/Display/#PC2: JSKT2.AA, JSKT2-3.7
/Display/#PC3: JSKT2.BB, JSKT2-3.8
/Display/#PC4: JSKT2.CC, JSKT2-3.9
/Display/#PC5: JSKT2.DD, JSKT2-3.10
/Display/#PC6: JSKT2.EE, JSKT2-3.11
/Display/#PC7: JSKT2.FF, JSKT2-3.12
/Display/#PC8: JSKT2.GG, JSKT2-3.13
/Display/#PC9: JSKT2.HH, JSKT2-3.14
/Display/#PC10: JSKT2.JJ, JSKT2-3.15
/Display/#PC11: JSKT2.KK, JSKT2-3.16
/Display/#PC12: JSKT2.LL, JSKT2-3.17
/Display/#RESET-2-Z: JSKT3.HH, JSKT3-1.18
/Display/#SIP-30-Z: JSKT1.MM, JSKT1-3.20
/Display/#SOP-30-P: JSKT1.LL, JSKT1-3.19
/Display/#STOP-2-T: JSKT3.JJ, JSKT3-1.19
/Display/#STP-30-L: JSKT1.NN, JSKT1-1.1
/Display/#STR-30-H: JSKT1.PP, JSKT1-1.2
/Display/#X-57-D: JSKT1.JJ, JSKT1-3.17
/Display/#Y-57-Z: JSKT1.KK, JSKT1-3.18
/Display/+5vDisplay: J0.3, JSKT2.NN, JSKT3.MM
/Display/A1: JSKT1.W, JSKT1-2.1
/Display/A2: JSKT1.X, JSKT1-2.2
/Display/A3: JSKT1.Y, JSKT1-2.3
/Display/A4: JSKT1.Z, JSKT1-2.4
/Display/A5: JSKT1.~a~, JSKT1-2.5
/Display/A6: JSKT1.~b~, JSKT1-2.6
/Display/A7: JSKT1.~c~, JSKT1-2.7
/Display/A8: JSKT1.~d~, JSKT1-2.8
/Display/A9: JSKT1.~e~, JSKT1-2.9
/Display/A10: JSKT1.~f~, JSKT1-2.10
/Display/A11: JSKT1.~g~, JSKT1-2.11
/Display/A12: JSKT1.~h~, JSKT1-2.12
/Display/A13: JSKT1.~i~, JSKT1-2.13
/Display/A14: JSKT1.~j~, JSKT1-2.14
/Display/A15: JSKT1.~k~, JSKT1-2.15
/Display/A16: JSKT1.~m~, JSKT1-2.16
/Display/A17: JSKT1.~n~, JSKT1-2.17
/Display/A18: JSKT1.~p~, JSKT1-2.18
/Display/G1: JSKT1.B, JSKT1-1.3
/Display/G2: JSKT1.C, JSKT1-1.4
/Display/G3: JSKT1.D, JSKT1-1.5
/Display/G4: JSKT1.E, JSKT1-1.6
/Display/G5: JSKT1.F, JSKT1-1.7
/Display/G6: JSKT1.G, JSKT1-1.8
/Display/G7: JSKT1.H, JSKT1-1.9
/Display/G8: JSKT1.J, JSKT1-1.10
/Display/G9: JSKT1.K, JSKT1-1.11
/Display/G10: JSKT1.L, JSKT1-1.12
/Display/G11: JSKT1.M, JSKT1-1.13
/Display/G12: JSKT1.N, JSKT1-1.14
/Display/G13: JSKT1.P, JSKT1-1.15
/Display/G14: JSKT1.R, JSKT1-1.16
/Display/G15: JSKT1.S, JSKT1-1.17
/Display/G16: JSKT1.T, JSKT1-1.18
/Display/G17: JSKT1.U, JSKT1-1.19
/Display/G18: JSKT1.V, JSKT1-1.20
/Display/J1: JSKT2.W, JSKT2-1.19
/Display/J2: JSKT2.X, JSKT2-1.20
/Display/J3: JSKT2.Y, JSKT2-2.1
/Display/J4: JSKT2.Z, JSKT2-2.2
/Display/J5: JSKT2.~a~, JSKT2-2.3
/Display/J6: JSKT2.~b~, JSKT2-2.4
/Display/J7: JSKT2.~c~, JSKT2-2.5
/Display/J8: JSKT2.~d~, JSKT2-2.6
/Display/J9: JSKT2.~e~, JSKT2-2.7
/Display/J10: JSKT2.~f~, JSKT2-2.8
/Display/J11: JSKT2.~g~, JSKT2-2.9
/Display/J12: JSKT2.~h~, JSKT2-2.10
/Display/J13: JSKT2.~i~, JSKT2-2.11
/Display/J14: JSKT2.~j~, JSKT2-2.12
/Display/J15: JSKT2.~k~, JSKT2-2.13
/Display/J16: JSKT2.~m~, JSKT2-2.14
/Display/M1: JSKT2.B, JSKT2-1.1
/Display/M2: JSKT2.C, JSKT2-1.2
/Display/M3: JSKT2.D, JSKT2-1.3
/Display/M4: JSKT2.E, JSKT2-1.4
/Display/M5: JSKT2.F, JSKT2-1.5
/Display/M6: JSKT2.G, JSKT2-1.6
/Display/M7: JSKT2.H, JSKT2-1.7
/Display/M8: JSKT2.J, JSKT2-1.8
/Display/M9: JSKT2.K, JSKT2-1.9
/Display/M10: JSKT2.L, JSKT2-1.10
/Display/M11: JSKT2.M, JSKT2-1.11
/Display/M12: JSKT2.N, JSKT2-1.12
/Display/M13: JSKT2.P, JSKT2-1.13
/Display/M14: JSKT2.R, JSKT2-1.14
/Display/M15: JSKT2.S, JSKT2-1.15
/Display/M16: JSKT2.T, JSKT2-1.16
/Display/M17: JSKT2.U, JSKT2-1.17
/Display/M18: JSKT2.V, JSKT2-1.18
/Display/P1: JSKT2.~n~, JSKT2-2.15
/Display/P2: JSKT2.~p~, JSKT2-2.16
/Display/P3: JSKT2.~q~, JSKT2-2.17
/Display/P4: JSKT2.~r~, JSKT2-2.18
/Display/P5: JSKT2.~s~, JSKT2-2.19
/Display/P6: JSKT2.~t~, JSKT2-2.20
/Display/P7: JSKT2.~u~, JSKT2-3.1
/Display/P8: JSKT2.~v~, JSKT2-3.2
/Display/P9: JSKT2.~w~, JSKT2-3.3
/Display/P10: JSKT2.~x~, JSKT2-3.4
/Display/P11: JSKT2.~y~, JSKT2-3.5
/Display/Q1: JSKT1.~q~, JSKT1-2.19
/Display/Q2: JSKT1.~r~, JSKT1-2.20
/Display/Q3: JSKT1.~s~, JSKT1-3.1
/Display/Q4: JSKT1.~t~, JSKT1-3.2
/Display/Q5: JSKT1.~u~, JSKT1-3.3
/Display/Q6: JSKT1.~v~, JSKT1-3.4
/Display/Q7: JSKT1.~w~, JSKT1-3.5
/Display/Q8: JSKT1.~x~, JSKT1-3.6
/Display/Q9: JSKT1.~y~, JSKT1-3.7
/Display/Q10: JSKT1.~z~, JSKT1-3.8
/Display/Q11: JSKT1.AA, JSKT1-3.9
/Display/Q12: JSKT1.BB, JSKT1-3.10
/Display/Q13: JSKT1.CC, JSKT1-3.11
/Display/Q14: JSKT1.DD, JSKT1-3.12
/Display/Q15: JSKT1.EE, JSKT1-3.13
/Display/Q16: JSKT1.FF, JSKT1-3.14
/Display/Q17: JSKT1.GG, JSKT1-3.15
/Display/Q18: JSKT1.HH, JSKT1-3.16
GND: J0.2, JSKT1.A, JSKT2.A, JSKT3.A
